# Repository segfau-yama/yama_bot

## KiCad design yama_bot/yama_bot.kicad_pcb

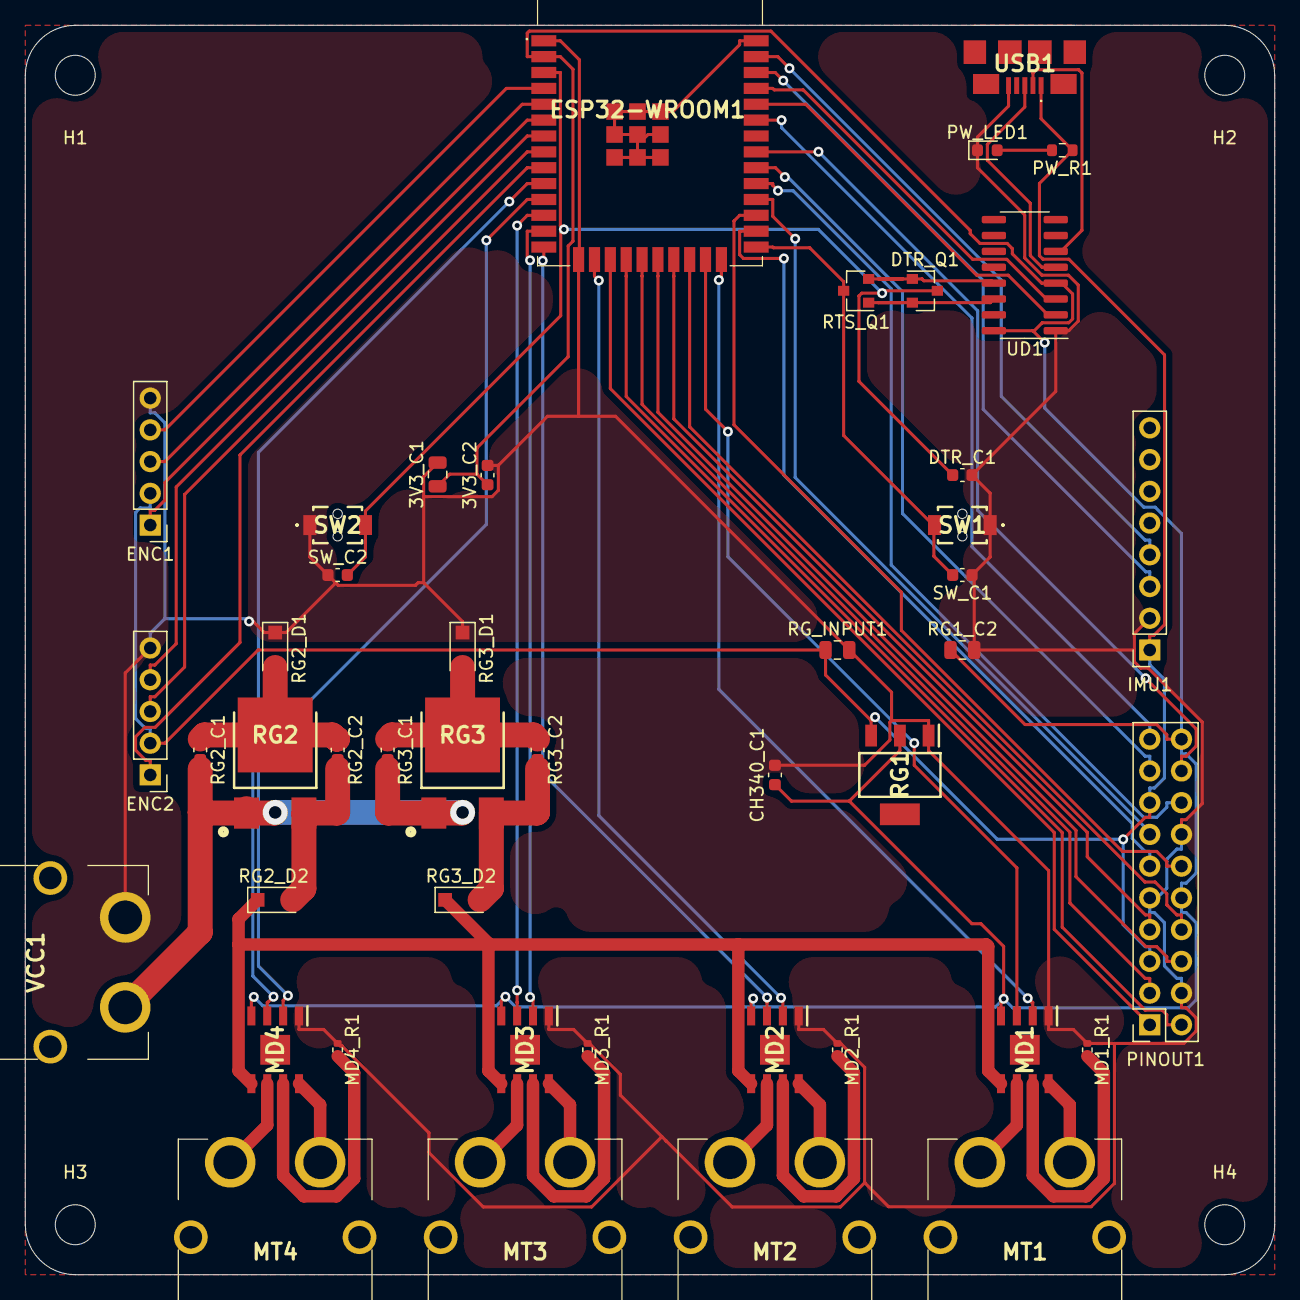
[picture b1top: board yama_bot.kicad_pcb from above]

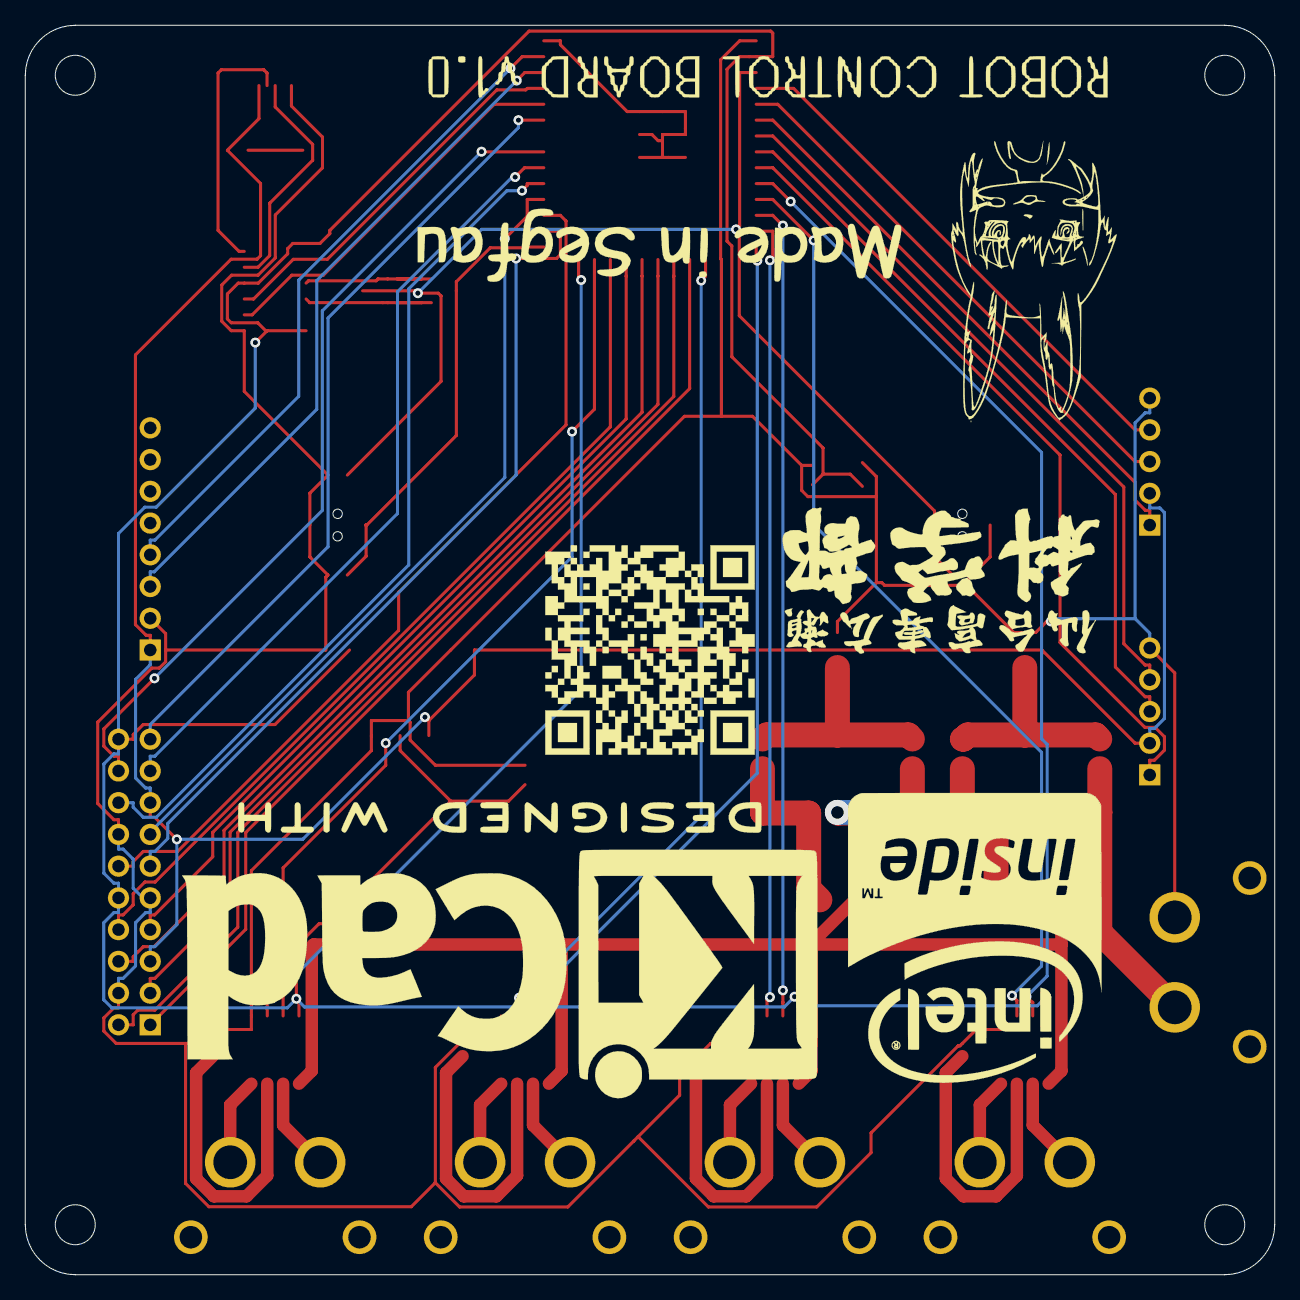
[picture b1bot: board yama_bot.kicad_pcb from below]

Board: 2 copper layers, 100.0 x 100.0 mm, 55 parts (6 on the bottom side), 60 nets.

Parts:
3V3_C1: 22u; C_0805_2012Metric
3V3_C2: 0.1u; C_0603_1608Metric
CH340_C1: 0.1u; C_0603_1608Metric
DTR_C1: 1u; C_0603_1608Metric
DTR_Q1: BSS138; SOT-23
ENC1, ENC2: Conn_01x05; PinHeader_1x05_P2.54mm_Vertical
ESP32-WROOM1: ESP32-WROOM-32_M103QH2800PH3Q0_; ESP32WROOM32M103QH2800PH3Q0
G1: LOGO; made_in_segfau
G2: LOGO; robot_ctrl_bd
G3: LOGO; miniqr
G4: KiCad-Logo2_20mm_SilkScreen
G5: LOGO; intel_inside2
G6: LOGO; sendaikousenhirose
H1, H2, H3, H4: MountingHole; MountingHole_3.2mm_M3
IMU1: Conn_01x08; PinSocket_1x08_P2.54mm_Vertical
MD1, MD2, MD3, MD4: TB67H450FNG,EL; SOIC127P600X175-9N
MD1_R1, MD2_R1, MD3_R1, MD4_R1: 0.5; R_0402_1005Metric
MT1, MT2, MT3, MT4: XT60PW-M; XT60PWM
PINOUT1: Conn_02x10_Counter_Clockwise; PinSocket_2x10_P2.54mm_Vertical
PW_LED1: LED; LED_0603_1608Metric
PW_R1: 1k; R_0603_1608Metric
RG1: LM1117-3.3; SOT230P700X180-4N
RG1_C2: 10u; C_0805_2012Metric
RG2, RG3: NJM7800S-DL1; TO-252-3-L1
RG2_C1, RG3_C1: 0.39u; C_0603_1608Metric
RG2_C2, RG3_C2: 0.1u; C_0603_1608Metric
RG2_D1, RG2_D2, RG3_D1, RG3_D2: D; D_SOD-123F
RG_INPUT1: 10u; C_0805_2012Metric
RTS_Q1: BSS138; SOT-23
SW1, SW2: SW_Push; TVAF06A020BR
SW_C1, SW_C2: 0.1u; C_0603_1608Metric
UD1: CH340G; SOIC-16_3.9x9.9mm_P1.27mm
USB1: USB_B_Micro; ZX62B5PA33
VCC1: XT60PW-M; XT60PWM

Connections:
+3V3: 3V3_C1.1, 3V3_C2.1, CH340_C1.1, ESP32-WROOM1.2, MD1.4, MD2.4, MD3.4, MD4.4, PINOUT1.10, PINOUT1.20, RG1.2, RG1_C2.1, UD1.4, UD1.16
+5V: ENC1.2, ENC2.2, IMU1.1, PINOUT1.5, PINOUT1.15, PW_R1.1, RG1.3, RG_INPUT1.1, USB1.1
+12V: MD1.5, MD2.5, MD3.5, MD4.5, RG2_D2.1, RG3_D2.1
DTR: DTR_C1.1, DTR_Q1.3, ESP32-WROOM1.3, SW2.2, SW_C2.2
ENC1_A: ENC1.3, ESP32-WROOM1.5
ENC1_B: ENC1.1, ESP32-WROOM1.6
ENC1_X: ENC1.4, ESP32-WROOM1.4
ENC2_A: ENC2.3, ESP32-WROOM1.8
ENC2_B: ENC2.1, ESP32-WROOM1.9
ENC2_X: ENC2.4, ESP32-WROOM1.7
GND: 3V3_C1.2, 3V3_C2.2, CH340_C1.2, DTR_C1.2, ENC1.5, ENC2.5, ESP32-WROOM1.1, ESP32-WROOM1.15, IMU1.2, MD1.1, MD1_R1.1, MD2.1, MD2_R1.1, MD3.1, MD3_R1.1, MD4.1, MD4_R1.1, PINOUT1.4, PINOUT1.9, PINOUT1.14, PW_LED1.1, RG1.1, RG1_C2.2, RG2_D1.1, RG3_D1.1, RG_INPUT1.2, SW1.1, SW2.1, SW_C1.1, SW_C2.1, UD1.1, USB1.5, VCC1.2
IMU_SCL: ESP32-WROOM1.36, IMU1.3
IMU_SDA: ESP32-WROOM1.37, IMU1.4
IO1: ESP32-WROOM1.17, PINOUT1.1
IO2: ESP32-WROOM1.18, PINOUT1.2
IO3: ESP32-WROOM1.19, PINOUT1.3
IO4: ESP32-WROOM1.20, PINOUT1.6
IO5: ESP32-WROOM1.21, PINOUT1.7
IO6: ESP32-WROOM1.22, PINOUT1.8
IO8: ESP32-WROOM1.26, PINOUT1.11
IO9: ESP32-WROOM1.27, PINOUT1.12
IO10: ESP32-WROOM1.28, PINOUT1.13
IO11: ESP32-WROOM1.29, PINOUT1.16
IO12: ESP32-WROOM1.30, PINOUT1.17
IO13: ESP32-WROOM1.31, PINOUT1.18
IO14: ESP32-WROOM1.33, PINOUT1.19
MT1_IN1: ESP32-WROOM1.23, MD1.3
MT1_IN2: ESP32-WROOM1.24, MD1.2
MT2_IN1: ESP32-WROOM1.14, MD2.3
MT2_IN2: ESP32-WROOM1.16, MD2.2
MT3_IN1: ESP32-WROOM1.12, MD3.3
MT3_IN2: ESP32-WROOM1.13, MD3.2
MT4_IN1: ESP32-WROOM1.10, MD4.3
MT4_IN2: ESP32-WROOM1.11, MD4.2
unnamed: DTR_Q1.1, RTS_Q1.2, UD1.13
unnamed: DTR_Q1.2, RTS_Q1.1, UD1.14
unnamed: ESP32-WROOM1.38, ESP32-WROOM1.39, ESP32-WROOM1.40, ESP32-WROOM1.41, ESP32-WROOM1.42, ESP32-WROOM1.43, ESP32-WROOM1.44, ESP32-WROOM1.45, ESP32-WROOM1.46, ESP32-WROOM1.47
unnamed: MD1.6, MT1.2
unnamed: MD1.7, MD1_R1.2
unnamed: MD1.8, MT1.1
unnamed: MD2.6, MT2.2
unnamed: MD2.7, MD2_R1.2
unnamed: MD2.8, MT2.1
unnamed: MD3.6, MT3.2
unnamed: MD3.7, MD3_R1.2
unnamed: MD3.8, MT3.1
unnamed: MD4.6, MT4.2
unnamed: MD4.7, MD4_R1.2
unnamed: MD4.8, MT4.1
unnamed: PW_LED1.2, PW_R1.2
unnamed: RG2.2, RG2_C2.2, RG2_D2.2
unnamed: RG2.3, RG2_C1.1, RG2_C2.1, RG2_D1.2
unnamed: RG3.2, RG3_C2.2, RG3_D2.2
unnamed: RG3.3, RG3_C1.1, RG3_C2.1, RG3_D1.2
unnamed: UD1.5, USB1.3
unnamed: UD1.6, USB1.2
RTS: ESP32-WROOM1.25, RTS_Q1.3, SW1.2, SW_C1.2
USB_RX: ESP32-WROOM1.34, UD1.2
USB_TX: ESP32-WROOM1.35, UD1.3
VCC: RG2.1, RG2_C1.2, RG3.1, RG3_C1.2, VCC1.1
